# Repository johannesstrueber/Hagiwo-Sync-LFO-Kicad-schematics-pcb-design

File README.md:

# HAGIWO's SYNC LFO Eurorack Module<br/> Work in Progress Schematics, PCBs, and Design Files 

In this repository, I digitalized HAGIWOs sketched schematics in Kicad and then created PCBs for the circuit and a front panel. I also created two design files. The first is for matching the drill holes of the panel with the placed components. The second is for labeling the components on the silkscreen layer of the panel.

***This is a work-in-progress project. Actually, this is my first layout. Take nothing for granted. The second revision is produced.*** 
<br/>
<br/>
**TODO** <br/>
<ul>
<li>Physical solution for wrong pot direction (currently software solution)</li>
<li>code for second inverted output (is in WIP status)</li>
<li>GND planes</li>
</ul>
<br/>

**Here are the in- and outputs. To get a idea of the module**
- Knob 1: AMP – amplifier control. The output voltage is set between 0 and 5 volts. 
- Knob 2: PHASE – phase control sets the phase
- Knob 3: waveform control 
- Knob 4: MOD – internal modulation, creates complex waveforms 
- Input 1:  CLK – clock in
- Output 1: OUT – output
- Output 2: INV – inverted output
<br/>

**KICAD Notes**
 - design_placement.svg is placed on layer USER 8
 - circuit layout is generated by the freerouting plugin
<br/>

**BOM**
|ID |Identifier                            |Footprint                                           |Amount|Description       |
|---|--------------------------------------|----------------------------------------------------|------|------------------|
|1  |D4,D3                                 |LED_D3.0mm                                          |2     |LED               |
|2  |RV3-FORM1,RV2-PHASE1,RV4-MOD1,RV1-AMP1|Potentiometer_Alps_RK09K_Single_Vertical            |4     |R_Potentiometer_US|
|3  |J1                                    |Jack_3.5mm_QingPu_WQP-PJ398SM_Vertical_CircularHoles|1     |CLOCK IN          |
|4  |J3                                    |Jack_3.5mm_QingPu_WQP-PJ398SM_Vertical_CircularHoles|1     |INV               |
|5  |J2                                    |Jack_3.5mm_QingPu_WQP-PJ398SM_Vertical_CircularHoles|1     |OUT               |
|6  |R10,R4,R6,R7,R1,R5                    |R_Axial_DIN0204_L3.6mm_D1.6mm_P2.54mm_Vertical      |6     |R 470             |
|7  |C4,C1,C3,C2                           |C_Disc_D4.3mm_W1.9mm_P5.00mm                        |4     |C 220pF           |
|8  |D2,D1                                 |D_DO-35_SOD27_P7.62mm_Horizontal                    |2     |BAT43             |
|9  |R9,R8                                 |R_Axial_DIN0204_L3.6mm_D1.6mm_P2.54mm_Vertical      |2     |R 33K             |
|10 |J4                                    |IDC-Header_2x05_P2.54mm_Vertical                    |1     |Connector_02x05   |
|11 |R3                                    |R_Axial_DIN0204_L3.6mm_D1.6mm_P2.54mm_Vertical      |1     |R 100K            |
|12 |C6,C5                                 |CP_Radial_D5.0mm_P2.50mm                            |2     |C 4.7 µF          |
|13 |A1                                    |Arduino_Nano                                        |1     |Arduino_Nano      |
|14 |R2                                    |R_Axial_DIN0204_L3.6mm_D1.6mm_P2.54mm_Vertical      |1     |R 1K              |

**CHANGELOG** <br/>
<br/>

**rev 0.2.1** <br/>
<ul>
<li>I adjusted the drilling diameter to 7.2mm to fit the threads of some potentiometers, e.g., t18. The previous front panel was made for rv09 potentiometers, which don't have a larger thread drilling.</li>
<li>the main pcb stays the same as 0.2.0</li>
</ul>
<br/>

**rev 0.2** <br/>
<ul>
<li> !!! changed pin order on connector </li>
<li> 10 pin connector instead of 16 pin</li>
<li> add missing 33k resistor for LED </li>
<li> resistors and capacitors now have values </li>
<li> larger gap setting for disc capacitors </li>
<li> code wrong direction potis</li>
<li> new design to match other upcoming modules </li>
<li> second output INV - inverted 
</ul>
<br/>

**rev 0.1** <br/>
<ul>
<li>first layout PRODUCED and working</li>
</ul>
<br/>

Hence, this is only trying to put HAGIWOs circuit into Kicad to create a PCB. You can find more information about the layout and functionality [ + here](https://note.com/solder_state/n/n4c600f2431c3) 
<br/>
<br/>

**Original Design and Code by HAGIWO** 
- [HAGIWO – note.com](https://note.com/solder_state)
- [HAGIWO – Twitter](https://twitter.com/HAGIWO1)
<br/>

**Fonts**
- [Rocko – Casady & Greene](https://moorstation.org/typoasis/designers/casady_greene/r_z.htm)
- [Tiny – Jack Halten Fahnestock](https://velvetyne.fr/fonts/tiny/)
<br/>

**Pictures of the produced rev 0.2**
<br/>
<br/>

<br/>

<br/>

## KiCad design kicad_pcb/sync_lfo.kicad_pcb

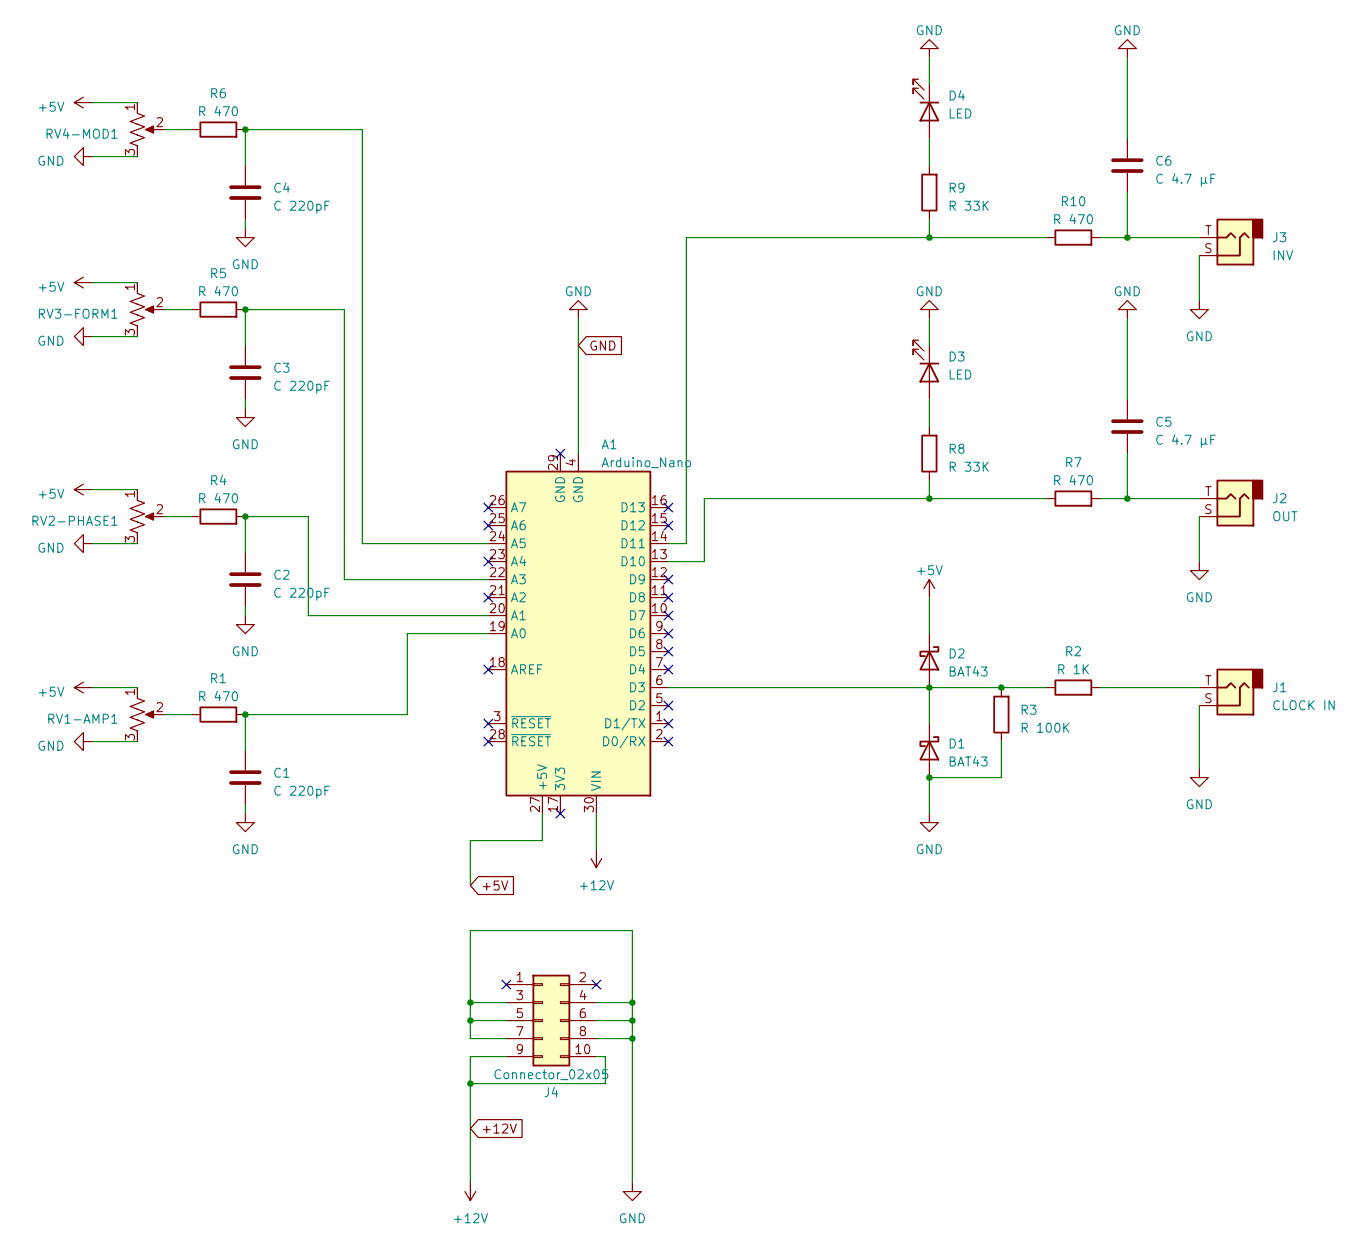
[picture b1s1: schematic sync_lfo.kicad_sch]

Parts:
A1: Arduino_Nano
C1, C2, C3, C4: C 220pF; C_Disc_D4.3mm_W1.9mm_P5.00mm
C5, C6: C 4.7 µF; C_Radial_D5.0mm_H11.0mm_P2.00mm
D1, D2: BAT43; D_DO-35_SOD27_P7.62mm_Horizontal
D3, D4: LED; LED_D3.0mm
J1: CLOCK IN; Jack_3.5mm_QingPu_WQP-PJ398SM_Vertical_CircularHoles
J2: OUT; Jack_3.5mm_QingPu_WQP-PJ398SM_Vertical_CircularHoles
J3: INV; Jack_3.5mm_QingPu_WQP-PJ398SM_Vertical_CircularHoles
J4: Connector_02x05; IDC-Header_2x05_P2.54mm_Vertical
R1, R4, R5, R6, R7, R10: R 470; R_Axial_DIN0204_L3.6mm_D1.6mm_P2.54mm_Vertical
R2: R 1K; R_Axial_DIN0204_L3.6mm_D1.6mm_P2.54mm_Vertical
R3: R 100K; R_Axial_DIN0204_L3.6mm_D1.6mm_P2.54mm_Vertical
R8, R9: R 33K; R_Axial_DIN0204_L3.6mm_D1.6mm_P2.54mm_Vertical
RV1-AMP1, RV2-PHASE1, RV3-FORM1, RV4-MOD1: R_Potentiometer_US; Potentiometer_Alps_RK09K_Single_Vertical

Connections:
+5V: A1.27 (+5V), D2.1 (K), RV1-AMP1.1, RV2-PHASE1.1, RV3-FORM1.1, RV4-MOD1.1
+12V: A1.30 (VIN), J4.9, J4.10
GND: A1.4 (GND), C1.2, C2.2, C3.2, C4.2, C5.1, C6.1, D1.2 (A), D3.1 (K), D4.1 (K), J1.S, J2.S, J3.S, J4.3, J4.4, J4.5, J4.6, J4.7, J4.8, R3.1, RV1-AMP1.3, RV2-PHASE1.3, RV3-FORM1.3, RV4-MOD1.3
unnamed: A1.19 (A0), C1.1, R1.2
unnamed: A1.20 (A1), C2.1, R4.2
unnamed: A1.22 (A3), C3.1, R5.2
unnamed: A1.24 (A5), C4.1, R6.2
unnamed: A1.6 (D3), D1.1 (K), D2.2 (A), R2.1, R3.2
unnamed: A1.13 (D10), R7.1, R8.1
unnamed: A1.14 (D11), R9.1, R10.1
unnamed: C5.2, J2.T, R7.2
unnamed: C6.2, J3.T, R10.2
unnamed: D3.2 (A), R8.2
unnamed: D4.2 (A), R9.2
unnamed: J1.T, R2.2
unnamed: R1.1, RV1-AMP1.2
unnamed: R4.1, RV2-PHASE1.2
unnamed: R5.1, RV3-FORM1.2
unnamed: R6.1, RV4-MOD1.2

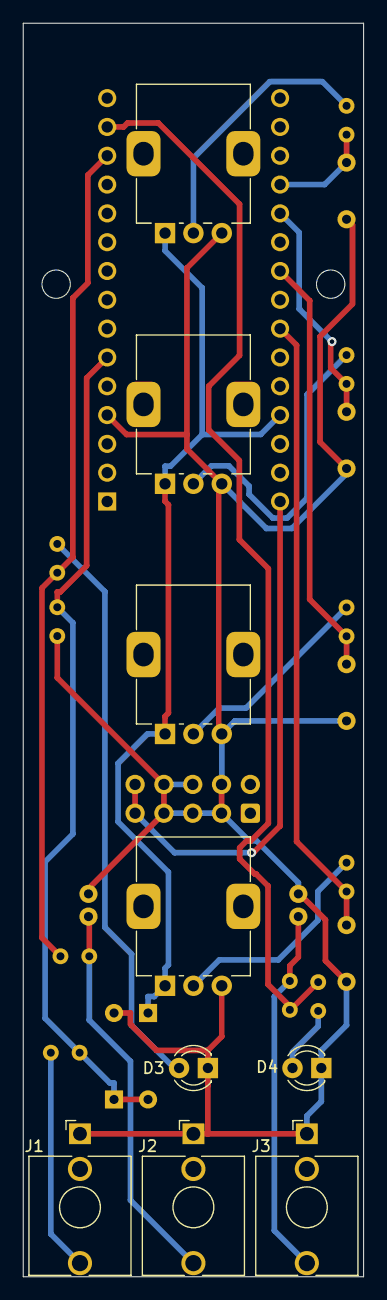
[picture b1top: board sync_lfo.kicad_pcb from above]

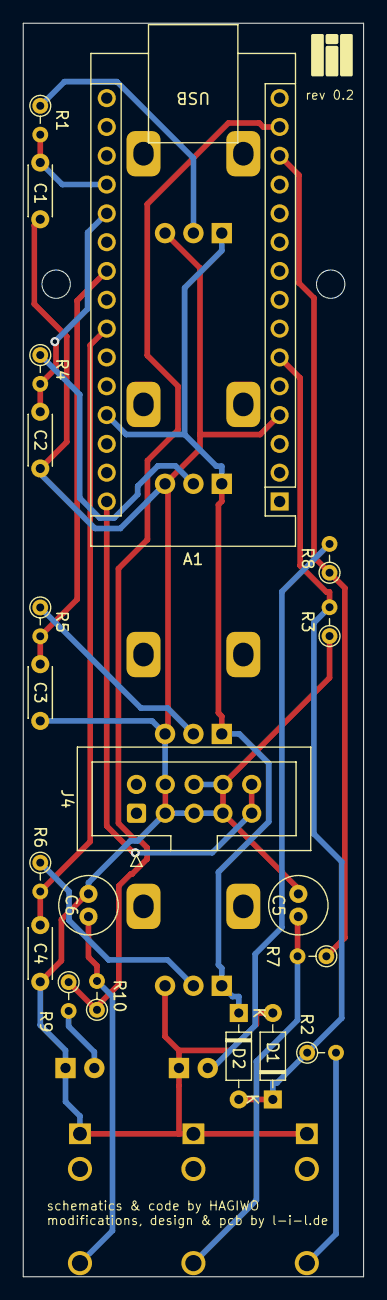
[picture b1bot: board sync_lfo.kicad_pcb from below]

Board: 2 copper layers, 30.0 x 110.5 mm, 30 parts (21 on the bottom side), 19 nets.

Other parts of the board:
HOLE RIGHT: MountingHole_2.5mm

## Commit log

2023-05-29 init
2023-05-29 add images to readme
2023-06-19 feat: :fire: remove unsused copper frontpanel
2023-06-19 feat: :bookmark: rev 0.2 frontpanel
2023-06-19 feat: :sparkles: rev 0.2 pcb and schematics
2023-06-25 feat: :sparkles: change code to match rotation direction
2023-06-25 feat: :sparkles: 10pin connector, drill holes, for distance, better routing
2023-07-03 feat: :lipstick: update design files, overall design system, clean placement file
2023-07-06 feat: :sparkles: inv output, new design, reposition
2023-07-06 feat: :lipstick: new design, placement files and inv output
2023-07-06 docs: :memo: update readme
2023-07-07 add screenshot of frontpanel rev 0.2
2023-07-27 feat: :sparkles: adjust potentiometer drillings to also fit potis with threads
2023-07-27 feat: :sparkles: add invert output to code WIP
2023-07-27 typo
2023-08-12 feat: :bug: correct max voltage
2023-08-24 add BOM.md
